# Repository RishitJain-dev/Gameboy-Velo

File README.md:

# Gameboy-Velo
Gameboy Velo is a modern take on the classic Gameboy, with a joystick instead of a d-pad, and the same A and B buttons as before. This new version includes a large colourful TFT screen and included storage with an SD card reader and even a LiPo battery!

It is programmed in C++, using Arduino IDE to compile! The micro controller is the XIAO ESP32-C3.

Total price is around $70 including filament and PCB prices. Please note that prices fluctuate! Check the BOM.csv for more detailed financial information.

### Features
- Analog Joystick
- 1080p Full Colour screen!
- 3 buttons
- Full Bluetooth and WiFi capabilities!

This project consists of 2 main parts, the PCB and CAD. The PCB was designed in KiCAD, while the CAD was made in Onshape. This project is fully open source for NON COMMERCIAL purposes.

### CAD
made in onshape! fits together with friction, but has screw holes in case your printer isnt as accurate. it uses 3 3d printed buttons, any colour you choose!

### schematic diagram!
took me way too long, its quite simple. look to this while soldering to know what's going on! I used labels instead of wires but remember that labels that have the same text are electrically connected.

### PCB
made in kicad! what the pcb looks like: (everything is a thru hole component so they can easily be hand-soldered.)

### Firmware
It uses arduino IDE to flash the code onto the XIAO. using C++, you can program the screen to run whatever game you choose. im currently working on a scratch game importer. they are stored on the screen's inbuilt SD card.

### BOM
please read bom.csv for more detailed financials and where to buy the parts, here is a uncomprehensive list of components:
- XIAO ESP32-C3
- 3 Push Buttons
- Analogue Joystick
- Adafruit TFT screen
- PCB
- 3D printed parts

### Credits 
to Stardance Hack club for funding this project!

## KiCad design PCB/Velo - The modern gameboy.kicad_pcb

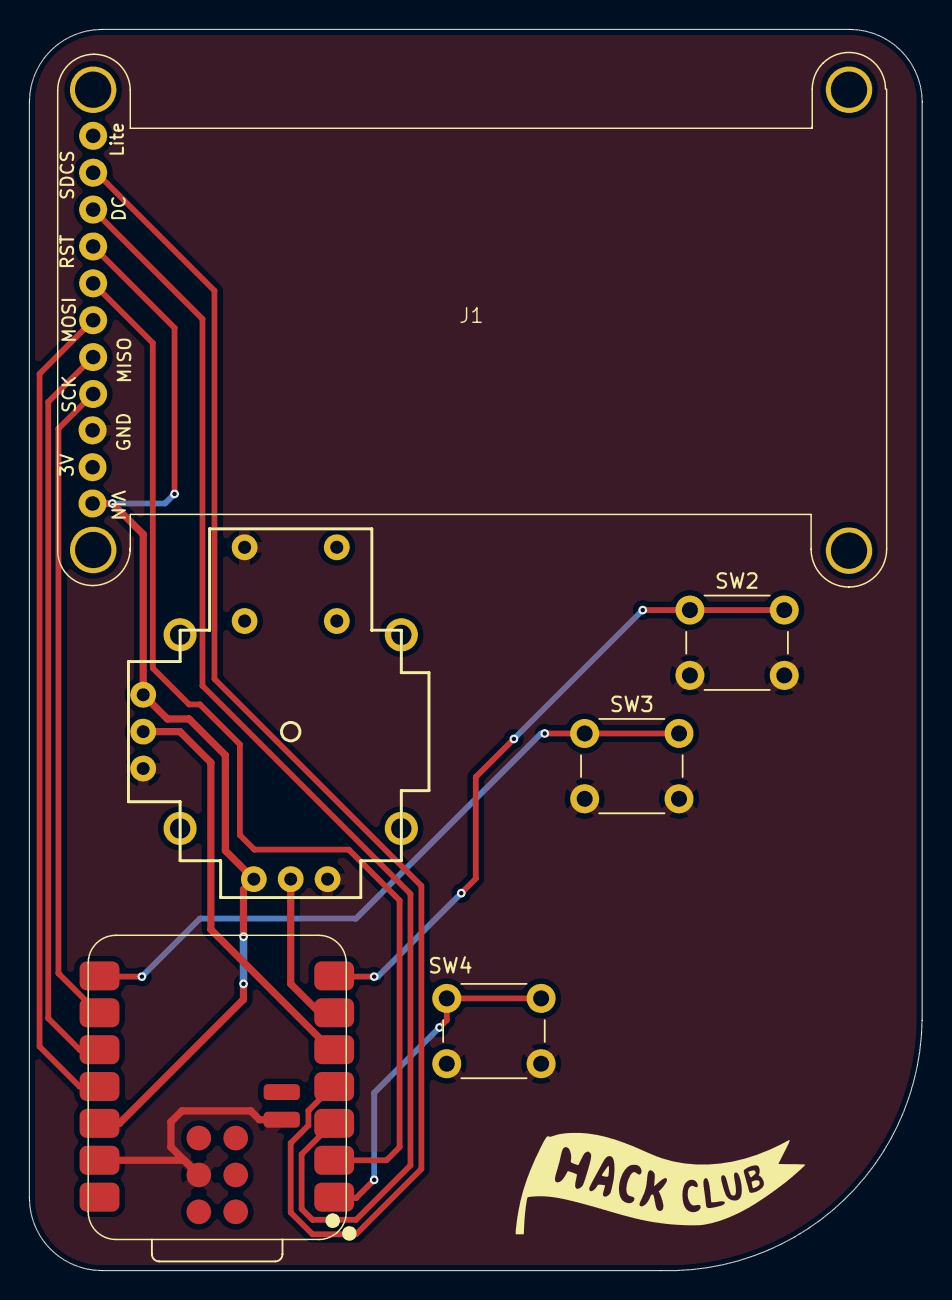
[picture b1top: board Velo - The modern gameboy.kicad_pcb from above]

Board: 2 copper layers, 61.5 x 85.5 mm, 6 parts (0 on the bottom side), 13 nets.

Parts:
J1: Conn_01x11_Pin; Adafruit 1.9 320x170 Colour IPS TFT Display (ST7789)
SW1: Joystick; Joystick_PTH
SW2, SW3, SW4: Push_Button; SW_PUSH_6mm
U1: XIAO-ESP32-C3-SMD

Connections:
3.3V: J1.1, J1.8, SW1.VCC, U1.12 (3V3_OUT)
/D0: SW4.1, U1.1 (D0)
/D1: J1.7, U1.2 (D1)
/D2: J1.9, U1.3 (D2)
/D3: J1.10, U1.4 (D3)
/D4: SW1.Vertical, U1.5 (D4)
/D5: SW1.Horizontal, U1.6 (D5)
/D6: SW2.1, U1.7 (D6)
/D7: SW3.1, U1.8 (D7)
/D8: J1.4, U1.9 (D8)
/D9: J1.5, U1.10 (D9/BOOT)
/D10: J1.6, U1.11 (D10)
GND: J1.3, SW1.GND, SW2.2, SW3.2, SW4.2, U1.13 (GND), U1.18 (GND), U1.22 (GND)
